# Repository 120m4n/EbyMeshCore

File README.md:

# EbyMeshCore

LoRa mesh node PCB: Pro Micro nRF52840 (nice!nano clone) + Ebyte E22-900M30S / E22-900M33S (SX1262), fed from an external 5 V (max 5.5 V) supply through an AMS1117-3.3 LDO. Targeted at [MeshCore](https://github.com/meshcore-dev/MeshCore) firmware.

> **This is a variant.** The hardware is [Ebytastic](https://github.com/Sobollion/Ebytastic) by [Sobollion](https://github.com/Sobollion), itself derived from [faketec v4](https://github.com/gargomoma/fakeTec_pcb). This repo ports the project to KiCad 10 and switches the firmware focus from Meshtastic to MeshCore. For the original photos, Meshtastic firmware images, Altium sources and the Russian README, see the upstream repo.

> **WARNING:** do not power the board from USB and the external 5 V input at the same time — it damages the LDO.

## Firmware

MeshCore variant `variants/ebytemesh/` in [120m4n/MeshCore-HJ7RMN](https://github.com/120m4n/MeshCore-HJ7RMN/tree/feature/ebytemesh), branch `feature/ebytemesh`.

- Reuses `variants/promicro` (faketec pinout = this PCB).
- `EbyteMeshBoard`: battery reports 0 mV (P0.31 floats, no battery).
- `EbyteMeshRadioWrapper`: clamps every `setTxPower()` to `MAX_LORA_TX_POWER`.
- Module selected in `[ebytemesh_module]`:
  - E22-900M30S: `LORA_TX_POWER=22`
  - E22-900M33S: `LORA_TX_POWER=8`, `MAX_LORA_TX_POWER=8` (33S PA input must stay ≤ 9 dBm)
- Envs: `EbyteMesh_repeater`, `EbyteMesh_companion_radio_usb`, `EbyteMesh_companion_radio_ble`.

Flash by copying the `.uf2` onto the Pro Micro's UF2 bootloader drive.

### Pinout (nRF52840)

| Function | Pin |
|---|---|
| SPI SCK / MOSI / MISO | P0.02 / P1.15 / P1.11 |
| LoRa CS | P1.13 |
| DIO1 | P0.10 |
| BUSY | P0.29 |
| RESET | P0.09 |
| RXEN | P0.17 |
| TXEN | driven by SX1262 DIO2 |
| TCXO | DIO3, 1.8 V |

## Power

- `+5v` comes only from J2 (`5V_IN`) and feeds the E22 VCC and the AMS1117 input.
- The Pro Micro 3V3 pin is tied directly to the AMS1117 output (`+3.3v`); VBUS is not on the header.
- **USB only:** the MCU and 3.3 V loads (I2C, SW_OUT, pull-ups) run, but the E22 is unpowered → radio init fails. Fine for flashing/config only.
- USB can't drive the radio without a hardware change (e.g. Schottky VBUS → `+5v`), and 500 mA is below the E22's 600–670 mA TX current at 30 dBm (more at 33 dBm).
- Supply: 5 V, 1 A (1.3 A peak for the 33S).

## Repository layout

| Path | Contents |
|---|---|
| `EbyMeshCore.kicad_pro` / `.kicad_pcb` | KiCad 10 project; the PCB (imported from Altium) is the source of truth |
| `EbyMeshCore.kicad_sch` | Schematic reconstructed after import (PDF: `Docs/EbyMeshCore_schematic.pdf`) |
| `EbyMeshCore.kicad_sym`, `EbyMeshCore.pretty/` | Project-local symbol and footprint libraries |
| `production/` | JLCPCB outputs (Fabrication Toolkit): Gerbers, BOM, positions |
| `Docs/` | E22 datasheets, Pro Micro nRF52840 schematic |

## BOM

- Pro Micro nRF52840 (nice!nano clone)
- Ebyte E22-900M30S or E22-900M33S
- AMS1117-3.3
- Electrolytic cap 100 µF 16 V (220 µF better)
- Ceramic caps: 2× 0.1 µF, 1 µF, 4.7 µF
- Push buttons
- SMA-F edge connector
- Optional: MOSFETs (SOT-23) for peripherals, 10 kΩ I2C pull-ups

Full BOM with JLCPCB parts: `production/bom.csv`.

## TODO: E22P-915M30S

Same footprint and wiring, but pin 6 is a FEM enable that must be HIGH in both TX and RX (current firmware drives it as RXEN → LOW during TX). Fix: `-D EBYTE_E22P` + `radio.setRfSwitchTable(...)` on P0.17 (STBY LOW, RX HIGH, TX HIGH). E22P allows 22 dBm input (`LORA_TX_POWER=22`) and has VCC max 5.25 V — feed 5.0 V. Not implemented yet.

## Credits

- [Sobollion](https://github.com/Sobollion) for [Ebytastic](https://github.com/Sobollion/Ebytastic) — [support the original author](https://pay.cloudtips.ru/p/c197b86d)
- [gargomoma](https://github.com/gargomoma) for [faketec](https://github.com/gargomoma/fakeTec_pcb)
- [lupusworax](https://github.com/lupusworax) for the [faketec v4](https://github.com/gargomoma/fakeTec_pcb/issues/16) sources

## License

See [LICENSE](LICENSE).

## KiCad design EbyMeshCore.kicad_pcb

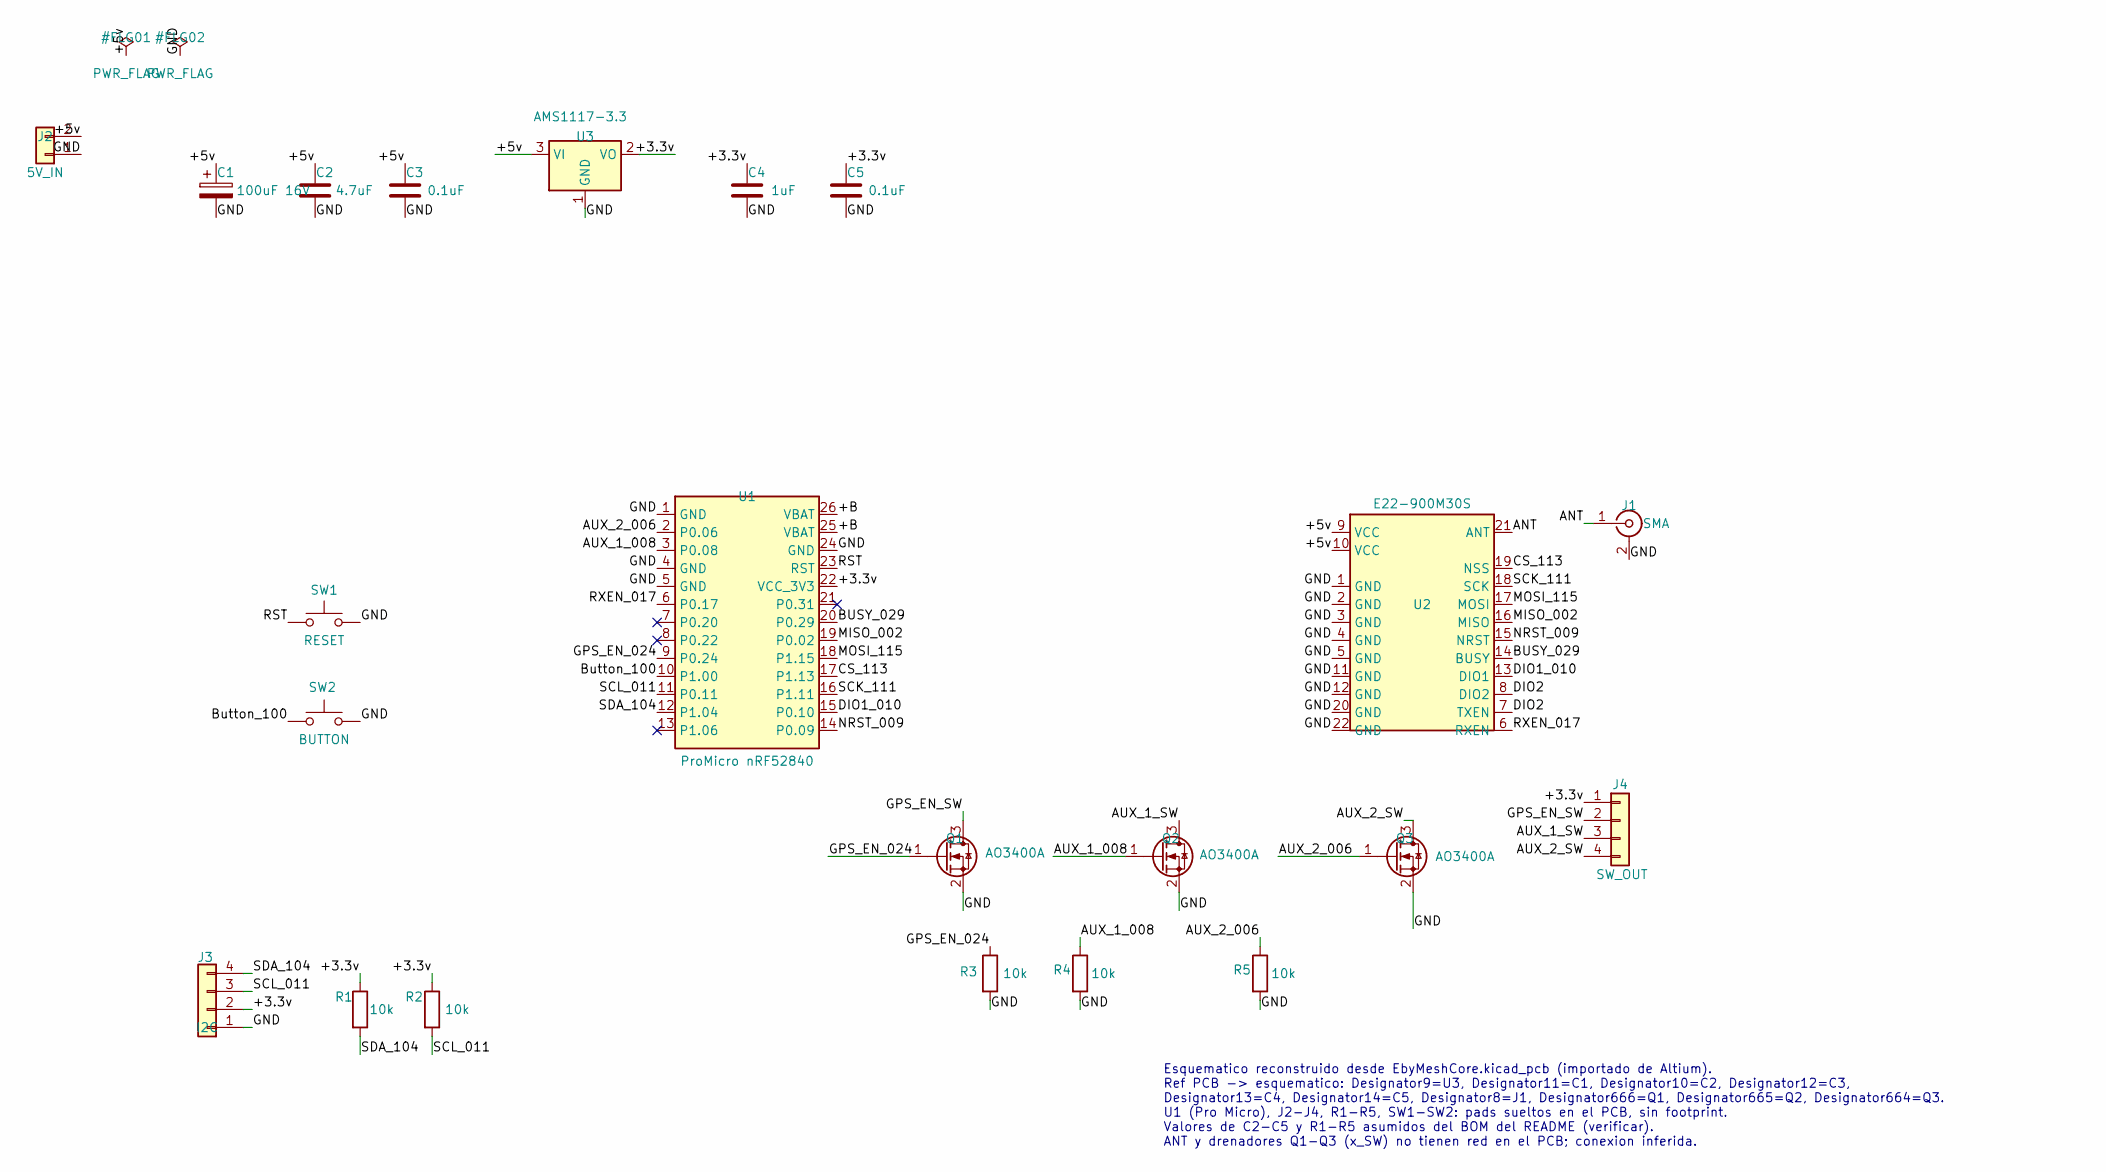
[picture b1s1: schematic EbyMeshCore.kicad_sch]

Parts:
C1: 100uF 16V; WCAP-AS5H_D6.3H7.7; LCSC C2164703
C2: 4.7uF; FP-CC1206-1_25-MFG; LCSC C29823
C3, C5: 0.1uF; FP-C1206C-EB-MFG; LCSC C24497
C4: 1uF; CAPC1206(3216)130_N; LCSC C1848
J1: SMA; FP-CON-SMA-EDGE-S-MFG; LCSC C5356059
J2: 5V_IN; PinHeader_5V_IN_1x02
J3: I2C; PinHeader_I2C_1x04
J4: SW_OUT; SolderPads_SW_OUT
Q1, Q2, Q3: AO3400A; SOT23-3
R1, R2, R3, R4, R5: 10k; R_1206_EbyMeshCore; LCSC C17902
SW1: RESET; SW_Push_2pad
SW2: BUTTON; SW_Push_2pad
U1: ProMicro nRF52840; ProMicro_nRF52840_2x13
U2: E22-900M30S; WIRELM-SMD_E22-900M30S
U3: AMS1117-3.3; FP-AMS1117-IPC_C

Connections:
106: U1.13 (P1.06)
+3.3v: C4.1, C5.1, J3.2, J4.1, R1.1, R2.1, U1.22 (VCC_3V3), U3.2 (VO), U3.4
+5v: C1.1, C2.1, C3.1, J2.2, U2.9 (VCC), U2.10 (VCC), U3.3 (VI)
+B: U1.25 (VBAT), U1.26 (VBAT)
ANT: J1.1 (In), U2.21 (ANT)
AUX_1 008: Q2.1 (G), R4.1, U1.3 (P0.08)
AUX_1_SW: J4.3, Q2.3 (D)
AUX_2 006: Q3.1 (G), R5.1, U1.2 (P0.06)
AUX_2_SW: J4.4, Q3.3 (D)
BUSY 029: U1.20 (P0.29), U2.14 (BUSY)
Batt% 031: U1.21 (P0.31)
Button 100: SW2.1, U1.10 (P1.00)
CS 113: U1.17 (P1.13), U2.19 (NSS)
DIO1 010: U1.15 (P0.10), U2.13 (DIO1)
DIO2: U2.7 (TXEN), U2.8 (DIO2)
GND: C1.2, C2.2, C3.2, C4.2, C5.2, J1.2 (Ext), J1.3, J1.4, J1.5, J2.1, J3.1, Q1.2 (S), Q2.2 (S), Q3.2 (S), R3.2, R4.2, R5.2, SW1.2, SW2.2, U1.1 (GND), U1.4 (GND), U1.5 (GND), U1.24 (GND), U2.1 (GND), U2.2 (GND), U2.3 (GND), U2.4 (GND), U2.5 (GND), U2.11 (GND), U2.12 (GND), U2.20 (GND), U2.22 (GND), U3.1 (GND)
GPS_EN 024: Q1.1 (G), R3.1, U1.9 (P0.24)
GPS_EN_SW: J4.2, Q1.3 (D)
GPS_RX 020: U1.7 (P0.20)
GPS_TX 022: U1.8 (P0.22)
MISO 002: U1.19 (P0.02), U2.16 (MISO)
MOSI 115: U1.18 (P1.15), U2.17 (MOSI)
NRST 009: U1.14 (P0.09), U2.15 (NRST)
RST: SW1.1, U1.23 (RST)
RXEN 017: U1.6 (P0.17), U2.6 (RXEN)
SCK 111: U1.16 (P1.11), U2.18 (SCK)
SCL 011: J3.3, R2.2, U1.11 (P0.11)
SDA 104: J3.4, R1.2, U1.12 (P1.04)

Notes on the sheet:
Esquematico reconstruido desde EbyMeshCore.kicad_pcb (importado de Altium). Ref PCB -> esquematico: Designator9=U3, Designator11=C1, Designator10=C2, Designator12=C3, Designator13=C4, Designator14=C5, Designator8=J1, Designator666=Q1, Designator665=Q2, Designator664=Q3. U1 (Pro Micro), J2-J4, R1-R5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

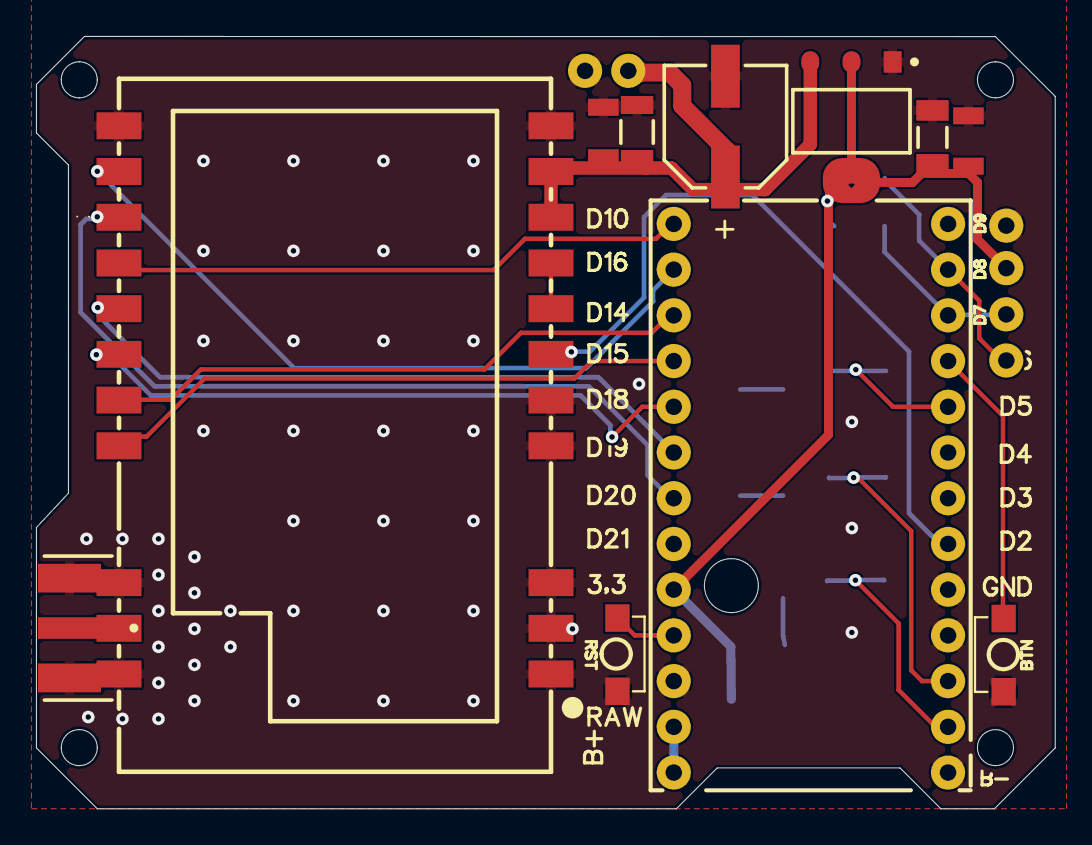
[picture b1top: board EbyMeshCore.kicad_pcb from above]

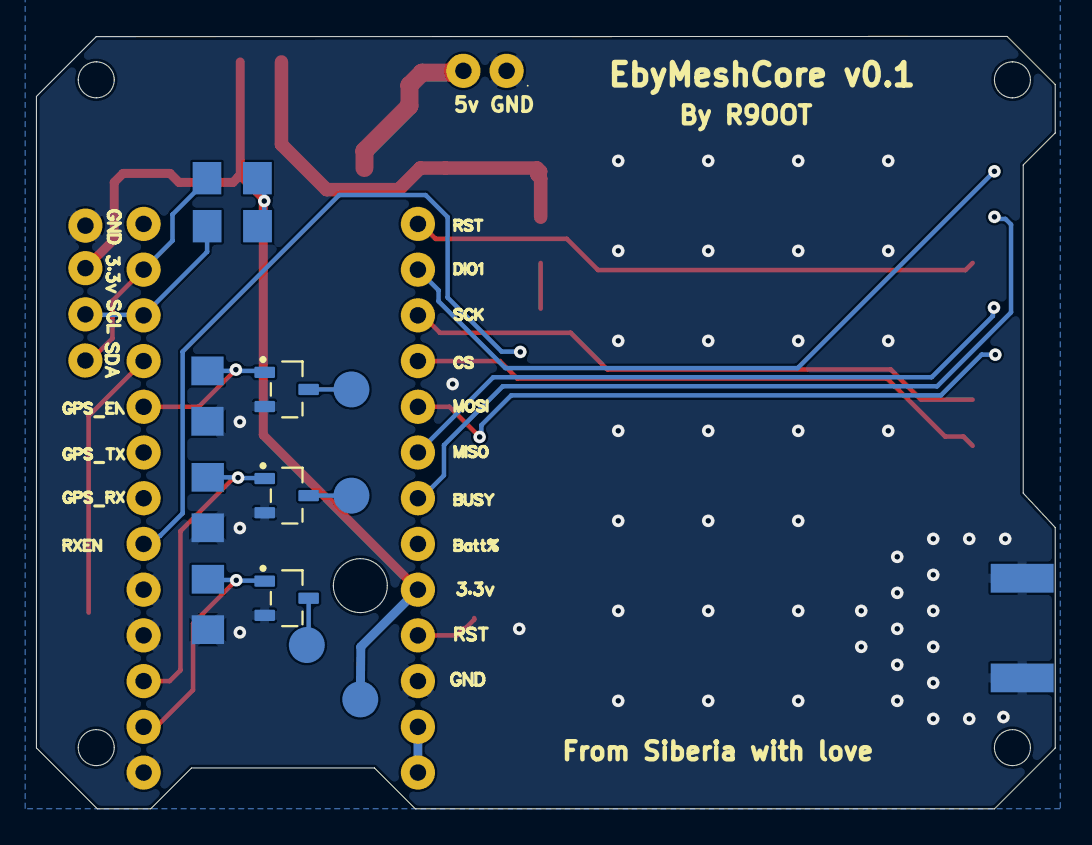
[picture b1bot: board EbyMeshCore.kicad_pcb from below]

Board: 2 copper layers, 56.6 x 42.9 mm, 22 parts (9 on the bottom side), 24 nets.

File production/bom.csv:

Designator,Footprint,Quantity,Value,LCSC Part #
C1,WCAP-AS5H_D6.3H7.7,1,100uF 16V,C2164703
C2,FP-CC1206-1_25-MFG,1,4.7uF,C29823
C3,FP-C1206C-EB-MFG,1,0.1uF,C24497
C4,CAPC1206(3216)130_N,1,1uF,C1848
C5,FP-C1206C-EB-MFG_C5,1,0.1uF,C24497
J1,FP-CON-SMA-EDGE-S-MFG,1,SMA,C5356059
Q1,SOT23-3_Q1,1,AO3400A,
Q2,SOT23-3,1,AO3400A,
Q3,SOT23-3_Q3,1,AO3400A,
"R1, R2",R_1206_EbyMeshCore,2,10k,C17902
R3,R_1206_EbyMeshCore_R3,1,10k,C17902
R4,R_1206_EbyMeshCore_R4,1,10k,C17902
R5,R_1206_EbyMeshCore_R5,1,10k,C17902
U3,FP-AMS1117-IPC_C,1,AMS1117-3.3,
